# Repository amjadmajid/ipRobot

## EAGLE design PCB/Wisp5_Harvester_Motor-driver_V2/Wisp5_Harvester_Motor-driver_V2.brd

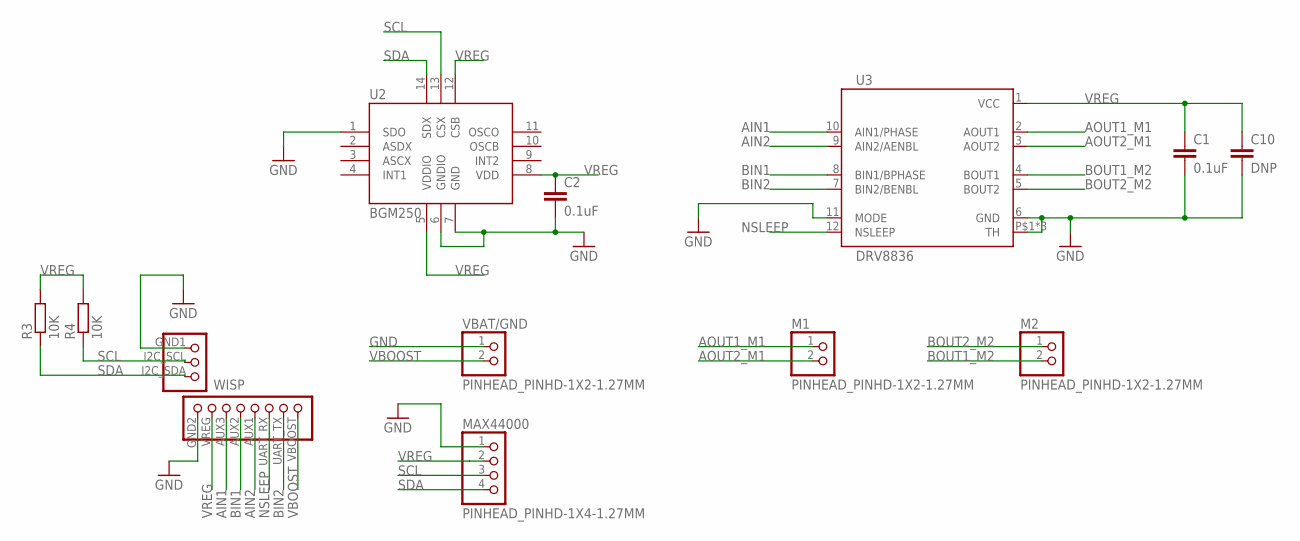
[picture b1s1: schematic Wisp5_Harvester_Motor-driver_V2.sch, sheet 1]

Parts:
C1, C2: 0.1uF; C0805
C10: DNP; C0805
M1, M2: PINHEAD_PINHD-1X2-1.27MM; PINHEAD_1X02-1.27MM
MAX44000: PINHEAD_PINHD-1X4-1.27MM; PINHEAD_1X04-1.27MM
R3, R4: 10K; R0805
U2: BGM250; LGA14L
U3: DRV8836; 12WSON
VBAT/GND: PINHEAD_PINHD-1X2-1.27MM; PINHEAD_1X02-1.27MM
WISP: WISP_HEADER; PINHEAD_WISP3X8-1.27MM

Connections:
AIN1: U3.10 (AIN1/PHASE), WISP.AUX3
AIN2: U3.9 (AIN2/AENBL), WISP.AUX1
AOUT1_M1: M1.1, U3.2 (AOUT1)
AOUT2_M1: M1.2, U3.3 (AOUT2)
BIN1: U3.8 (BIN1/BPHASE), WISP.AUX2
BIN2: U3.7 (BIN2/BENBL), WISP.UART_TX
BOUT1_M2: M2.2, U3.4 (BOUT1)
BOUT2_M2: M2.1, U3.5 (BOUT2)
GND: C1.2, C2.2, C10.2, MAX44000.1, U2.1 (SDO), U2.6 (GNDIO), U2.7 (GND), U3.6 (GND), U3.11 (MODE), U3.P$1 (TH), U3.P$2 (TH), U3.TH, VBAT/GND.1, WISP.GND1, WISP.GND2; also elsewhere on the board
NSLEEP: U3.12 (NSLEEP), WISP.UART_RX
SCL: MAX44000.3, R4.1, U2.13 (CSX), WISP.I2C_SCL
SDA: MAX44000.4, R3.1, U2.14 (SDX), WISP.I2C_SDA
VBOOST: VBAT/GND.2, WISP.VBOOST
VREG: C1.1, C2.1, C10.1, MAX44000.2, R3.2, R4.2, U2.5 (VDDIO), U2.8 (VDD), U2.12 (CSB), U3.1 (VCC), WISP.VREG; also elsewhere on the board

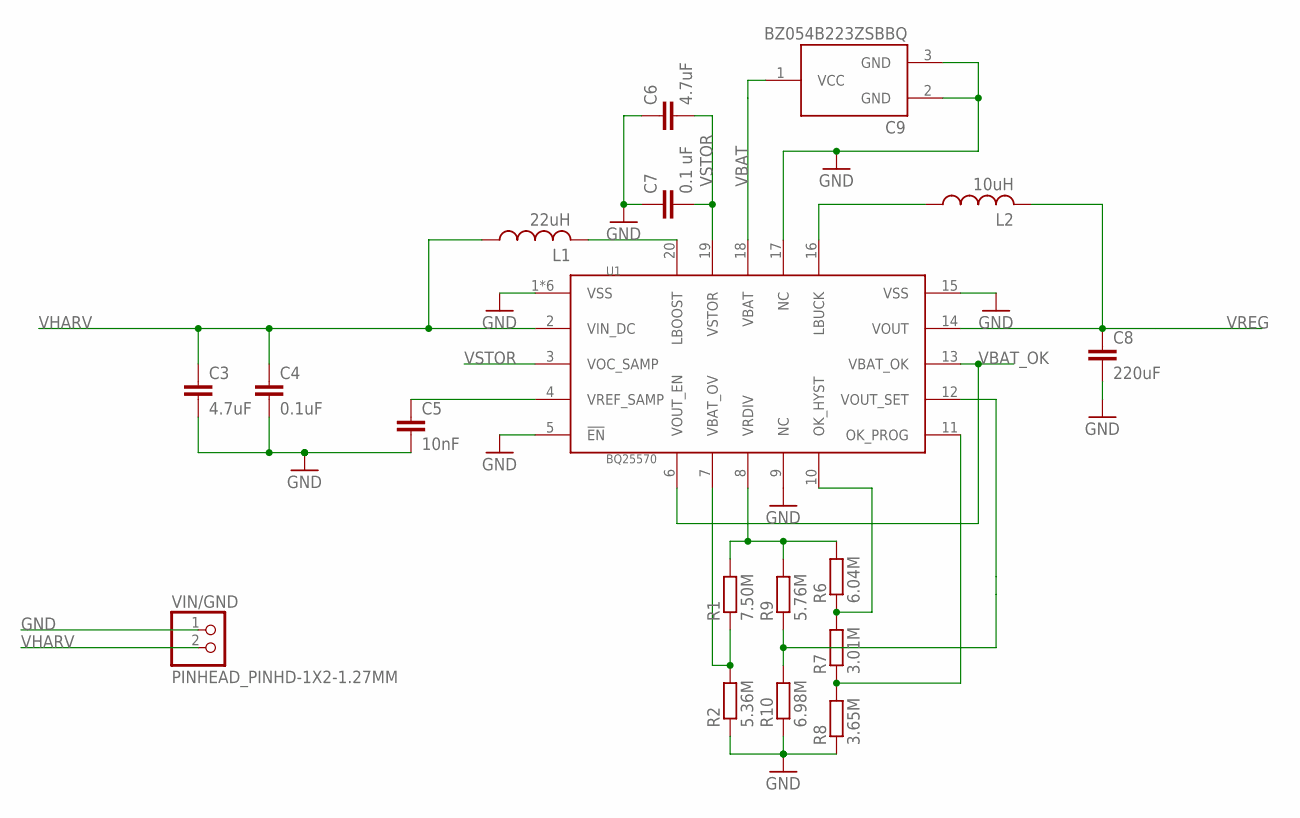
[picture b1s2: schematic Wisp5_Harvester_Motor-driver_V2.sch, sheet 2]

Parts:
C3, C6: 4.7uF; C0805
C4: 0.1uF; C0805
C5: 10nF; C0805
C7: 0.1 uF; C0805
C8: 220uF; C1210
C9: BZ054B223ZSBBQ; BZ05_S-STYLE
L1: 22uH; LPS4018
L2: 10uH; LPS4018
R1: 7.50M; R0805
R2: 5.36M; R0805
R6: 6.04M; R0805
R7: 3.01M; R0805
R8: 3.65M; R0805
R9: 5.76M; R0805
R10: 6.98M; R0805
U1: BQ25570; VQFN20
VIN/GND: PINHEAD_PINHD-1X2-1.27MM; PINHEAD_1X02-1.27MM

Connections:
GND: C3.2, C4.2, C5.2, C6.1, C7.1, C8.2, C9.2 (GND), C9.3 (GND), R2.1, R8.1, R10.1, U1.1 (VSS), U1.5 (!EN), U1.9 (NC), U1.15 (VSS), U1.17 (NC), U1.PWR_PAD (VSS), U1.PWR_PAD1 (VSS), U1.PWR_PAD2 (VSS), U1.PWR_PAD3 (VSS), U1.PWR_PAD4 (VSS), VIN/GND.1; also elsewhere on the board
unnamed: R9.1, R10.2, U1.12 (VOUT_SET)
unnamed: R1.2, R6.2, R9.2, U1.8 (VRDIV)
unnamed: L1.2, U1.20 (LBOOST)
unnamed: C5.1, U1.4 (VREF_SAMP)
unnamed: R6.1, R7.2, U1.10 (OK_HYST)
unnamed: L2.1, U1.16 (LBUCK)
unnamed: R1.1, R2.2, U1.7 (VBAT_OV)
unnamed: R7.1, R8.2, U1.11 (OK_PROG)
VBAT: C9.1 (VCC), U1.18 (VBAT)
VBAT_OK: U1.6 (VOUT_EN), U1.13 (VBAT_OK)
VHARV: C3.1, C4.1, L1.1, U1.2 (VIN_DC), VIN/GND.2
VREG: C8.1, L2.2, U1.14 (VOUT); also elsewhere on the board
VSTOR: C6.2, C7.2, U1.3 (VOC_SAMP), U1.19 (VSTOR)

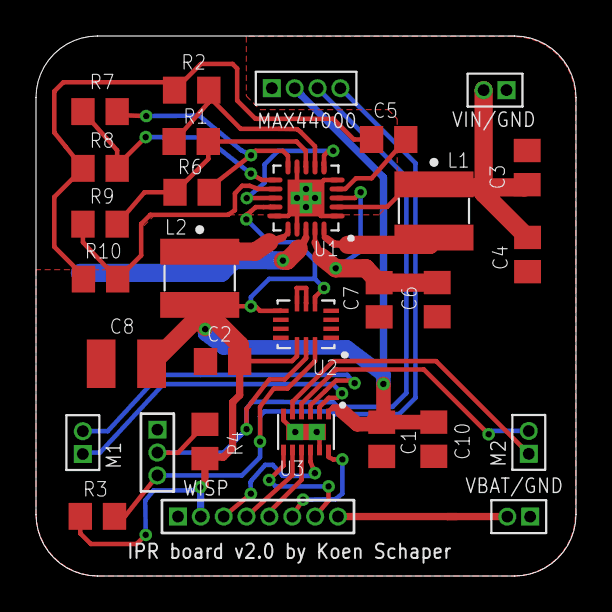
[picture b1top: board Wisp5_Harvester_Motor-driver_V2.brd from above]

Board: 2 copper layers, 30.0 x 30.0 mm, 30 parts (1 on the bottom side), 26 nets.

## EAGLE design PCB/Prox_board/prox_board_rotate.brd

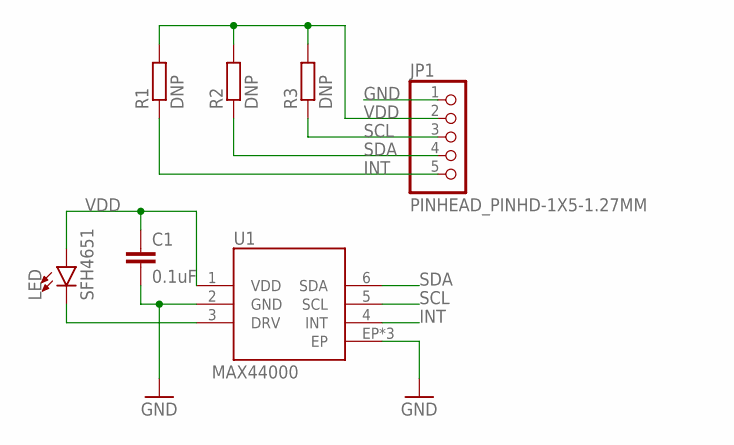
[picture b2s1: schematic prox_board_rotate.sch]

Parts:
C1: 0.1uF; C0603
JP1: PINHEAD_PINHD-1X5-1.27MM; PINHEAD_1X05-1.27MM
LED: SFH4651; MIDLED
R1, R2, R3: DNP; R0603
U1: MAX44000; 6OTDFN-EP

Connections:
GND: C1.2, JP1.1, U1.2 (GND), U1.EP, U1.P$1 (EP), U1.P$2 (EP)
INT: JP1.5, R1.1, U1.4 (INT)
unnamed: LED.C, U1.3 (DRV)
SCL: JP1.3, R3.1, U1.5 (SCL)
SDA: JP1.4, R2.1, U1.6 (SDA)
VDD: C1.1, JP1.2, LED.A, R1.2, R2.2, R3.2, U1.1 (VDD)

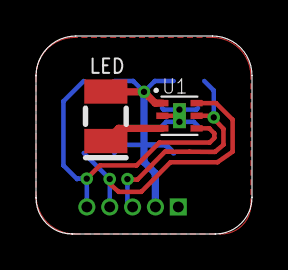
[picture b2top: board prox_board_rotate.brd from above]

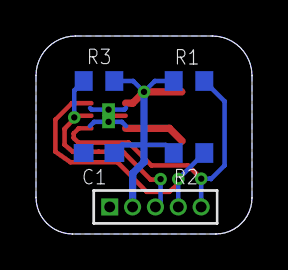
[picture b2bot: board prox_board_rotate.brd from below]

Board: 2 copper layers, 12.0 x 11.0 mm, 7 parts (5 on the bottom side), 6 nets.

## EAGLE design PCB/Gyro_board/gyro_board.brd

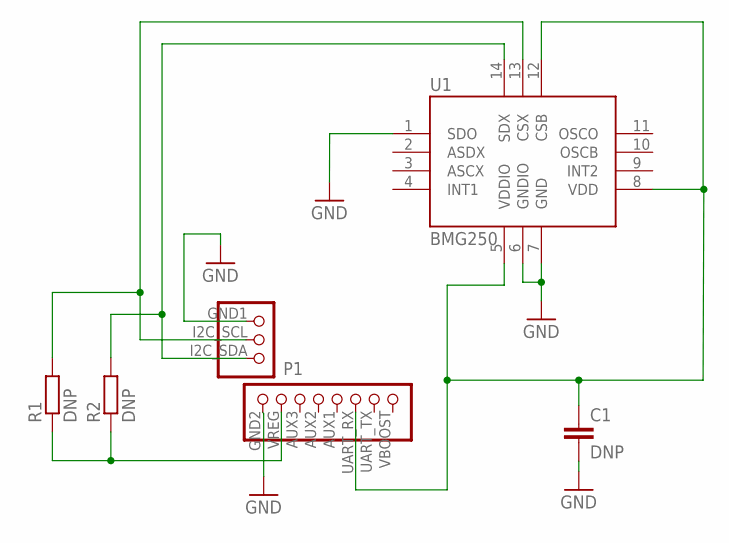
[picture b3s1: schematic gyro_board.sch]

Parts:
C1: DNP; C0603
P1: WISP_HEADER; PINHEAD_WISP3X8-1.27MM
R1, R2: DNP; R0603
U1: BMG250; LGA14L

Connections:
GND: C1.2, P1.GND1, P1.GND2, U1.1 (SDO), U1.6 (GNDIO), U1.7 (GND)
SCL: P1.I2C_SCL, R1.2, U1.13 (CSX)
SDA: P1.I2C_SDA, R2.2, U1.14 (SDX)
VEN: C1.1, P1.UART_RX, U1.5 (VDDIO), U1.8 (VDD), U1.12 (CSB)
VREG: P1.VREG, R1.1, R2.1

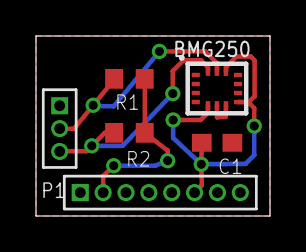
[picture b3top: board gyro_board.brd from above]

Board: 2 copper layers, 13.0 x 10.0 mm, 5 parts (0 on the bottom side), 5 nets.

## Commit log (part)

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2017-07-04 Update gitignore
2017-07-05 Cleanup
2017-07-05 Abstract steppermotor control
2017-07-06 Update model
2017-07-08 Work in progress
2017-07-10 Upload python model files
2017-07-11 Upload DC intermittently powered robot files
2017-07-12 Simple example to drive the dc motor.
2017-07-12 Increase i2c clk to 400khz
2017-07-13 Pwm control of the motor + method to disable the timer
2017-07-16 Rewritten part about locomotion
2017-07-16 Ramp pwm to decrease startup current when driving two motors!
2017-07-23 Added another reference!
2017-07-24 Added the unmaned nano aerial vehicle reference!
2017-07-24 Working example pwm for both motors -> going kind of straight!
2017-07-24 Removed parts about the stepper motors, localization and locomotion
2017-07-24 Only return the z-axis gyroscope data
2017-07-24 Also fix gyroscope for DC project
2017-07-24 Timer based checkpointing!
2017-07-27 Save progress robot pcb design v2
2017-07-28 Added proximity header and fixed layout
2017-07-31 Update schematic
2017-07-31 Updated packages
2017-07-31 Removed some small separate packages
2017-08-01 Working example of using timer B0 to drive forward and backward!
2017-08-01 Changed output pins so they work with wisp timer directly and also changed M2 (right) ground and power order
2017-08-01 Read gyro and added python file from other dc_motor_direct_h branch
2017-08-01 Fixed read_gyro.py, only read the required lines!!
2017-08-02 Upload board without routing and the library for the parts!
2017-08-02 Routing WIP
2017-08-02 Go straight for different speeds upto 40% pwm!
2017-08-03 Increased sample frequency to 400Hz and now using a PD controller
2017-08-03 Ramp to 700 and goes straight!!
2017-08-04 Increased Kp and Kd using the following steps (recommended answer): https://robotics.stackexchange.com/questions/167/what-are-good-strategies-for-tuning-pid-loops
2017-08-05 Finished routing + fixed drv8836
2017-08-05 Tend vias and added stop to powerpad vias!
2017-08-05 Fix the naming on the pcb and of the parts!
2017-08-06 Rotated header, to make it fit the mainboard!
2017-08-06 Fix naming and silkscreen on the back of the board!
2017-08-06 Added powering pervasive computing systems reference!
2017-08-07 Add a exta bulk capacitor near the hbridge!
2017-08-07 Checkpointing over approx 2 meter
2017-08-07 Revert chapter naming and remove old text
2017-08-08 Small changes to the layout and added missing inductor values!
2017-08-08 Final design for proximity and harvester board
2017-08-08 Update main and remove some old text
2017-09-04 Use a timer for the loop and removed the data ready check from the gyro because it slows down the loop significantly!
2017-09-06 Change sample / loop frequency to 50Hz and implemented a PI controller
2017-09-06 Fix bib entry!
2017-09-06 Moved paper content to thesis!
2017-09-07 Separate function for computing the pid: http://brettbeauregard.com/blog/2011/04/improving-the-beginner%E2%80%99s-pid-sample-time/
2017-09-07 changing both left and right speeds seems to work good, but needs to be tested with the other motors
2017-09-10 Only one function for driving the motors, forward, reverse and stop! (Other files still need to be updated!)
2017-09-11 Working going straight just like in branch h2
2017-09-12 Fix sign (left and right motor ctrl) and cleanup
2017-09-13 Added commands for straight and turning, but a automated stop still needs to be inplemented!
2017-09-13 Use single define for the sample time!
2017-09-15 Implemented a distance and angle setpoint and automatically stops when these are reached!
2017-09-18 Persistent movement, currently only works for battery powered, probably due to exceeding max speed (solar powered)!
2017-09-20 Fix inductor naming! switched them around...
2017-09-21 Invert motor orientation so it corresponds to the new pcb!
2017-09-21 Fix battery header orientation!
2017-09-22 Save report progress
2017-09-22 Increase gyroscope resolution!
2017-09-23 Revert "Invert motor orientation so it corresponds to the new pcb!"
    This reverts commit 25458353622f66f5e7fd83711e1725967b6ee760.
2017-09-23 Fix left and right + new minimal calibration values!
2017-09-24 Fixed turning, use just a simple p controller and increased sample frequency to 100Hz
2017-09-25 Include first line in read from output.hex file!!
2017-09-26 Reset values to zero on disabling the loop and include angle in command loop
2017-09-26 Method to save array to a file!
2017-09-26 Exclude minimal_speed.c from project!
2017-09-27 Reduce i2c frequency to 100kHz and use the submainclock for the control loop timer as well using a divider
2017-09-27 Include proximity sensor
2017-09-27 preface is located in chapters and not in template
2017-09-27 Updated text, mostly things TODO!
2017-09-27 Back to rmin and lmin!!
2017-09-27 Added debug defines for storing fram!
2017-09-28 Save new calibration values for turning!
2017-09-28 Make motor stop more imidiate!
2017-09-28 Final tuning for straight!
2017-09-28 Save progress on pid tuning!
2017-09-28 Proximity cleanup and added some extra comments
2017-09-29 Save and restore the angle + cleanup
2017-09-29 Simplify main!
2017-09-29 Number of loops can only be positive!
2017-09-29 Cleanup and consistency fix
2017-09-29 Set new stepp offset margins!
2017-09-29 Added extra todo's
2017-09-29 Save figure, not fully finisched!
2017-09-30 Modified random number generator to use timer A3
2017-09-30 Added comment for pi
2017-10-01 Added component references
2017-10-01 Written Hardware Implementation introduction
2017-10-01 Update energy harvesting section!
2017-10-01 Remove double Problem statement
2017-10-02 Added comments and moved pieces of text around
2017-10-05 Added a power interrupt timer that creates a brownout interrupt after a certain time
2017-10-06 Move delay right after init and before the gyroscope is initialized
2017-10-06 duplicate name fix in bibtex
2017-10-06 Small part about RF experiment in evaluation
2017-10-09 Added grid and xmin to distanc bat plot
2017-10-09 Update latex files, mainly introduction + moved some parts around
2017-10-09 Save experiment data!
2017-10-09 Upload latex text ideas
2017-10-09 Add 30gram experiment
2017-10-11 Save light experiment
2017-10-11 Save data
2017-10-12 Save experiment data and python plot
2017-10-12 Save min speed experiment data (half way)
2017-10-13 Renamed plot and added cost of parts
2017-10-13 Updated cost_of_parts.xlsx
2017-10-16 Upload motor frame and added 20 sec speed calibration@ 40 target
2017-10-16 Update light experiment data from digikey panel (in parallel now)
2017-10-16 Update light experiment data
2017-10-16 Remove unused data_size define
2017-10-16 update struct naming for non-volatile var
2017-10-17 Use robot config because each robot is different
2017-10-17 do not upload hex
2017-10-19 Upload missing experiment data
2017-10-20 Update experiment data
2017-10-23 Update experiment data!
2017-10-24 Save updated current consumed table!
2017-10-24 Save energy measurment data
2017-10-27 Remove Stepp offset!
2017-10-27 Disable motors at zero setpoint!
2017-10-27 Fixed curved movements with intermittency!
2017-10-29 Make radius static
2017-10-30 Cleanup repository according to updated gitignore!
2017-10-30 Fix right and left turning!
2017-10-30 Save turn calibrated values!
2017-10-31 Update the integration section
2017-10-31 Small changes to the robot design chapter
2017-11-01 Update light experiment results
2017-11-02 Created a preliminaries chapter and started on the stepper motor section
2017-11-02 Update related work text
2017-11-03 Update text
2017-11-03 Make figures uniform
2017-11-03 Fix reference and added reference to banggood solarpanel
2017-11-03 Added reference to the monsoon powermonitor
2017-11-04 Save the first version of the introduction!
2017-11-04 Small changes to the introduction
2017-11-06 Move the rf energy harvesting section to preliminaries for now
2017-11-06 Update table with cost in euro
2017-11-06 Update evaluation and introduction
2017-11-07 Mearsure led power consumption as well
2017-11-07 Update robot_tracking and upload rangedetector
2017-11-07 Update robot tracking
2017-11-07 Move model to robot preliminaries
2017-11-08 Update implementation section!
2017-11-08 Update Robot table
2017-11-08 First draft of limitations and future work
2017-11-08 Small updates
2017-11-09 Upload speed / pwm relation data!
2017-11-09 Update table to find speed
2017-11-10 Convert pixel data to cm and plot in matplotlib!
2017-11-10 Set x and y limits for plotting
2017-11-10 Update robot_tracking
2017-11-11 Update gitignore to only ignore video folders and modified robot_tracking.py to save data in csv
2017-11-11 Update robot_tracking!
2017-11-11 Upload circle pwm 50 data
2017-11-11 Upload square pwm 70 data
2017-11-11 Upload square pwm 30 data
2017-11-11 Upload straight pwm 70 data
2017-11-11 Upload straight 50 pwm data
2017-11-11 Update movement evaluation section
2017-11-12 Cleanup data
2017-11-12 Fixed plotting for each of the three pwm speeds
2017-11-12 set pwm trough variable
2017-11-12 Upload progress in evaluation
2017-11-12 Update evaluation
2017-11-13 Update tex files!
2017-11-13 Update introductions according to comments, needs more work
2017-11-13 Make het different movements selectable!
2017-11-13 Single plot per movement!
2017-11-13 Fix plot
2017-11-14 Add temporary movement evaluation
2017-11-14 Update stepper motor preliminaries
2017-11-14 Update related work!
2017-11-15 Fix formula's and other small fixes to implementation!
2017-11-16 Update robots table weight and cost roverables
2017-11-18 Upload simulink cd motor model!
2017-11-18 Save python implementation of motor model!
2017-11-19 Small fixes and comment!
2017-11-19 Function to generate square wave ie 50% duty cycle!
2017-11-20 Working pwm function!
2017-11-20 Fix wheel diameter and output distance
2017-11-20 Small fixes + robots table!
2017-11-20 Make tables uniform
2017-11-20 Added schematic to appendix
2017-11-20 Fix bibtex + small fixes
2017-11-21 Update transiently powered systems!
2017-11-21 Update evaluation added table!
2017-11-21 Save changes to model!
2017-11-22 Update introduction and related work according to feedback
2017-11-22 Update latex according to feedback
2017-11-22 Small updates!
2017-11-22 Fix artifacts and update plot movements
2017-11-23 Add outside solar experiments
2017-11-23 Update distance between number and unit!
2017-11-24 Update frontcover with photo of robot!
2017-11-25 Use single plot function!
2017-11-26 Update python and excel files!
2017-11-27 Update design and preliminaries!
2017-11-27 Update preliminaries!!
2017-11-27 Update preliminaries
2017-11-27 Update experimental data stepper motor!
2017-11-27 Update figure, might need one with pwm?
2017-11-28 Update plotmovement!
2017-11-28 Update circle estimate
2017-11-28 Add missing figures!
2017-11-28 Upload updated plot files!
2017-11-28 Update Evaluation seciton
2017-11-29 Update deviation from circle table, error in mean calulation!
2017-11-29 Update main
2017-11-29 Update files from solar experiments
2017-11-29 Update solar experiment data!
2017-11-30 Final values for length of movement
2017-11-30 Update evaluation!
2017-11-30 Fix and update references + design and implmentation section!
2017-12-01 Update preface!
2017-12-01 Update future work!
2017-12-01 Small changes to the preliminaries and update presentation date
2017-12-01 Fix bibtex authors if companies!
2017-12-02 Updated design and implementation!
2017-12-02 Update control design!
2017-12-03 Update preface and thesis outline
2017-12-03 Small fixes!
2017-12-04 Small fixes and updated tabel to use size squared
2017-12-05 Update abstract
2017-12-05 Update thesis small fixes and remove model for now!
2017-12-05 Update figure text and other small fixes
2017-12-06 Text update
2017-12-06 Update robot implementation figure
2017-12-07 Update text according to feedback
2017-12-07 Remove will!
2017-12-07 Update text and figures!
2017-12-08 Update abstract and preface!
2017-12-08 Update figures and small changes
2017-12-08 Update flowchart of code!
2017-12-10 Stage current measurements pwm 40%
2017-12-10 Latex presentation!
2017-12-10 Fixed stupid mistakes abstract!
2017-12-10 Update latex according to comments menno
2017-12-10 Rename target to duty cycle!
2017-12-10 Bigger robot implementation figure!
2017-12-10 Added embedded software logo to frontcover!
2017-12-11 Update design and implementation
2017-12-11 Upload thesis!
2017-12-12 Update presentation
